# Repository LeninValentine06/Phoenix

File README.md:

# LoRa-Based Real-Time Landslide Detection System
   
   *Figure 1: Slave Node PCB Design*

   *Figure 2: Master Node PCB Design*

## 1. Project Overview

### The Problem

Landslides are devastating natural disasters that claim thousands of lives annually worldwide. Traditional monitoring systems are often expensive, difficult to deploy in remote areas, and lack real-time alerting capabilities. Many vulnerable communities, especially in developing regions, lack access to early warning systems that could save lives.

### Our Solution

The LoRa-Based Real-Time Landslide Detection System provides an affordable, open-source solution for early detection and warning of potential landslide events. By combining low-power sensors, long-range wireless communication, and intelligent data processing, our system can:

- Detect early signs of land movement and soil condition changes
- Transmit data over long distances even in remote areas
- Provide immediate, multi-modal alerts to communities at risk
- Operate for extended periods on battery power

The system uses distributed ESP32-based sensor nodes placed in landslide-prone areas to continuously monitor ground movement, soil moisture, and environmental conditions. When potential landslide indicators are detected, the system triggers immediate alerts via multiple channels.

## 2. System Architecture

### Hardware Components

#### Sensor Node (ESP32)
- **Microcontroller**: ESP32-WROOM-32
- **Sensors**:
  - MPU6050 (3-axis accelerometer and gyroscope)
  - Capacitive soil moisture sensor
  - DHT22/AM2302 temperature and humidity sensor
- **Communication**: LoRa RA-02 module (433MHz)
- **Power**: 3.7V LiPo battery with solar charging capability

#### Master Node (ESP32)
- **Microcontroller**: ESP32-WROOM-32
- **Alert Mechanisms**:
  - 9V speaker/buzzer for audio alerts
  - 2.8" ILI9341 TFT display for visual alerts and status
  - Optional GSM module for SMS alerts
- **Communication**:
  - LoRa RA-02 module (433MHz)
  - WiFi/Bluetooth (for configuration and notifications)
- **Power**: 5V DC power supply with battery backup

### Data Flow Architecture

```
┌─────────────────┐     LoRa     ┌─────────────────┐     Alert     ┌─────────────────┐
│                 │  Wireless    │                 │   Triggers    │                 │
│   Sensor Node   │ ───────────► │   Master Node   │ ───────────► │  Alert Systems  │
│     (ESP32)     │    433MHz    │     (ESP32)     │               │   - Speaker     │
│                 │              │                 │               │   - Display     │
│                 │              │                 │               │   - Mobile      │
└─────────────────┘              └─────────────────┘               └─────────────────┘
        │                                 ▲
        │                                 │
        │         LoRa Wireless           │
        └─────────────────────────────────┘
                (Multiple Nodes)
```

1. **Data Collection**: The ESP32 sensor nodes continuously monitor accelerometer data (ground movement), soil moisture levels, and environmental conditions.
2. **Data Processing**: Initial data processing occurs on the sensor nodes to identify concerning patterns before transmission.
3. **Data Transmission**: Processed data is transmitted via LoRa to the master node.
4. **Alert Analysis**: The ESP32 master node analyzes data from multiple sensor nodes and determines if alert thresholds are exceeded.
5. **Alert Distribution**: When potential landslide conditions are detected, the master node activates local alerts and sends notifications to configured devices.

## 3. Features

### Real-time Environmental Monitoring
- Continuous accelerometer data collection at 50Hz sample rate
- Soil moisture monitoring with 5-minute intervals
- Temperature and humidity readings every 15 minutes
- Local data processing to detect movement patterns indicative of landslides

### Long-Range, Low-Power Communication
- LoRa communication with 3-10km range (depending on terrain) using 433MHz frequency
- Optimized data packets to minimize transmission power
- Node power management for extended battery life (3-6 months on a single charge with solar support)
- Reliable mesh networking capabilities between multiple sensor nodes

### Multi-Modal Alert System
- High-decibel audio alarm for immediate local warning
- Visual alerts and system status on TFT display
- Optional mobile alerts via SMS or app notifications
- Configurable alert thresholds based on local conditions

### System Scalability
- Support for up to 50 sensor nodes per master node
- Expandable with multiple master nodes for larger coverage areas
- Modular design allowing for additional sensor types
- Open API for integration with existing warning systems

## 4. Setup & Installation

### Prerequisites

#### Hardware Requirements
- ESP32 development boards (for both sensor and master nodes)
- MPU6050 accelerometer/gyroscope module
- Soil moisture sensor (capacitive recommended)
- DHT22/AM2302 temperature & humidity sensor
- LoRa RA-02 modules (433MHz)
- 2.8" ILI9341 TFT display
- 9V speaker/buzzer
- 3.7V LiPo batteries with solar charging modules
- Power supplies, jumper wires, and prototyping boards

#### Software Requirements
- Arduino IDE (for ESP32 programming)
- Required libraries (included in the repository):
  - RadioHead library for LoRa communication
  - Adafruit MPU6050 library
  - Adafruit DHT sensor library
  - Adafruit GFX & ILI9341 libraries

### Sensor Node Setup

1. **Hardware Assembly**

   Connect the components to the ESP32 according to this pinout:
   
   ```
   ESP32 (Sensor Node)   |     Component
   ------------------------------------
   GPIO21 (SDA)         ---    MPU6050 SDA
   GPIO22 (SCL)         ---    MPU6050 SCL
   GPIO36 (ADC0)        ---    Soil Moisture Sensor
   GPIO17               ---    DHT22 Data
   GPIO5 (SCK)          ---    RA-02 SCK
   GPIO23 (MOSI)        ---    RA-02 MOSI
   GPIO19 (MISO)        ---    RA-02 MISO
   GPIO18               ---    RA-02 CS
   GPIO14               ---    RA-02 RST
   GPIO26               ---    RA-02 DIO0
   5V                   ---    Battery + (via switch)
   GND                  ---    Common ground
   ```

*Figure 3: Serial Monitor Output from Slave Node showing sensor readings and LoRa transmission*

2. **Software Installation**

   a. Setup Arduino IDE for ESP32:
   - Add ESP32 board support to Arduino IDE
   - Install required libraries through the Library Manager

   b. Upload the sensor node code:
   - Clone this repository: `git clone https://github.com/LeninValentine06/lora-landslide-detection.git`
   - Navigate to the `sensor_node` directory
   - Open the `sensor_node.ino` file
   - Select your ESP32 board model and port
   - Compile and upload the code

### Master Node Setup

1. **Hardware Assembly**

   Connect the components to the ESP32 according to this pinout:
   
   ```
   ESP32 (Master Node)   |     Component
   ------------------------------------
   GPIO5 (SCK)          ---    RA-02 SCK
   GPIO23 (MOSI)        ---    RA-02 MOSI
   GPIO19 (MISO)        ---    RA-02 MISO
   GPIO18               ---    RA-02 CS
   GPIO14               ---    RA-02 RST
   GPIO26               ---    RA-02 DIO0
   GPIO25               ---    Speaker +
   GPIO21 (SDA)         ---    Display SDA
   GPIO22 (SCL)         ---    Display SCL
   GPIO2                ---    Display DC
   GPIO4                ---    Display CS
   GPIO15               ---    Display RST
   5V                   ---    Power input
   GND                  ---    Common ground
   ```

*Figure 4: Serial Monitor Output from Master Node showing received data and alert status*

2. **Software Installation**

   a. Setup Arduino IDE for ESP32:
   - Add ESP32 board support to Arduino IDE
   - Install required libraries through the Library Manager

   b. Upload the master node code:
   - Open the `/master_node/master_node.ino` file from the repository
   - Select your ESP32 board model and port
   - Compile and upload the code

### Optional Mobile Notification Setup

1. Install the companion mobile app (available in the `/mobile_app` directory)
2. Configure WiFi credentials in the master node code
3. Pair your smartphone with the master node using the app
4. Test the notification system by triggering a test alert

## 5. Usage Instructions

### Initial Configuration

1. Place sensor nodes in strategic locations based on landslide risk assessment
   - Ensure proper anchoring into stable ground
   - Position solar panels for optimal sunlight exposure
   - Maintain line-of-sight between nodes when possible

2. Power on the master node first, then the sensor nodes
   - The master node display will show initialization progress
   - Wait for "SYSTEM READY" message on the display

3. Configure alert thresholds using the master node interface:
   - Press the CONFIG button to enter setup mode
   - Adjust sensitivity, alert levels, and communication parameters
   - Save configuration when complete

### Normal Operation

Under normal conditions, the system will:
- Display current readings from all sensor nodes
- Show battery levels and signal strength
- Log data at regular intervals
- Perform automatic self-tests every 24 hours

The TFT display shows a grid of connected sensor nodes with their status. Green indicators show normal operation, yellow shows warning levels, and red indicates critical alerts.

### Alert Conditions

When potential landslide conditions are detected:

1. The master node will:
   - Activate the audio alarm
   - Display detailed alert information
   - Send notifications to paired mobile devices
   - Log the event with timestamp and sensor data

2. To acknowledge alerts:
   - Press the ACKNOWLEDGE button on the master node
   - The audio alarm will silence, but visual alerts remain
   - The system continues monitoring for worsening conditions

3. After the danger passes:
   - Press and hold RESET for 5 seconds
   - Confirm system reset when prompted
   - The system will return to normal monitoring mode

## 6. Contributing

Contributions to this project are welcome! Here's how you can help:

### Reporting Issues
- Use the GitHub issue tracker to report bugs
- Include detailed steps to reproduce the issue
- Attach logs or screenshots when available

### Pull Requests
1. Fork the repository
2. Create a new branch (`git checkout -b feature/your-feature-name`)
3. Make your changes
4. Run tests if available
5. Commit your changes (`git commit -m 'Add some feature'`)
6. Push to the branch (`git push origin feature/your-feature-name`)
7. Open a Pull Request

### Development Guidelines
- Follow existing code style and naming conventions
- Add comments to explain complex functionality
- Update documentation when making changes
- Add tests for new features when possible

## 7. License

This project is licensed under the Creative Commons Zero v1.0 Universal License - see the [LICENSE](LICENSE) file for details.

This means you can copy, modify, distribute and perform the work, even for commercial purposes, all without asking permission.

---

**Disclaimer**: This system is designed as an early warning tool but should not replace proper evacuation procedures or professional geological assessment. Always follow local authority guidance during emergency situations.

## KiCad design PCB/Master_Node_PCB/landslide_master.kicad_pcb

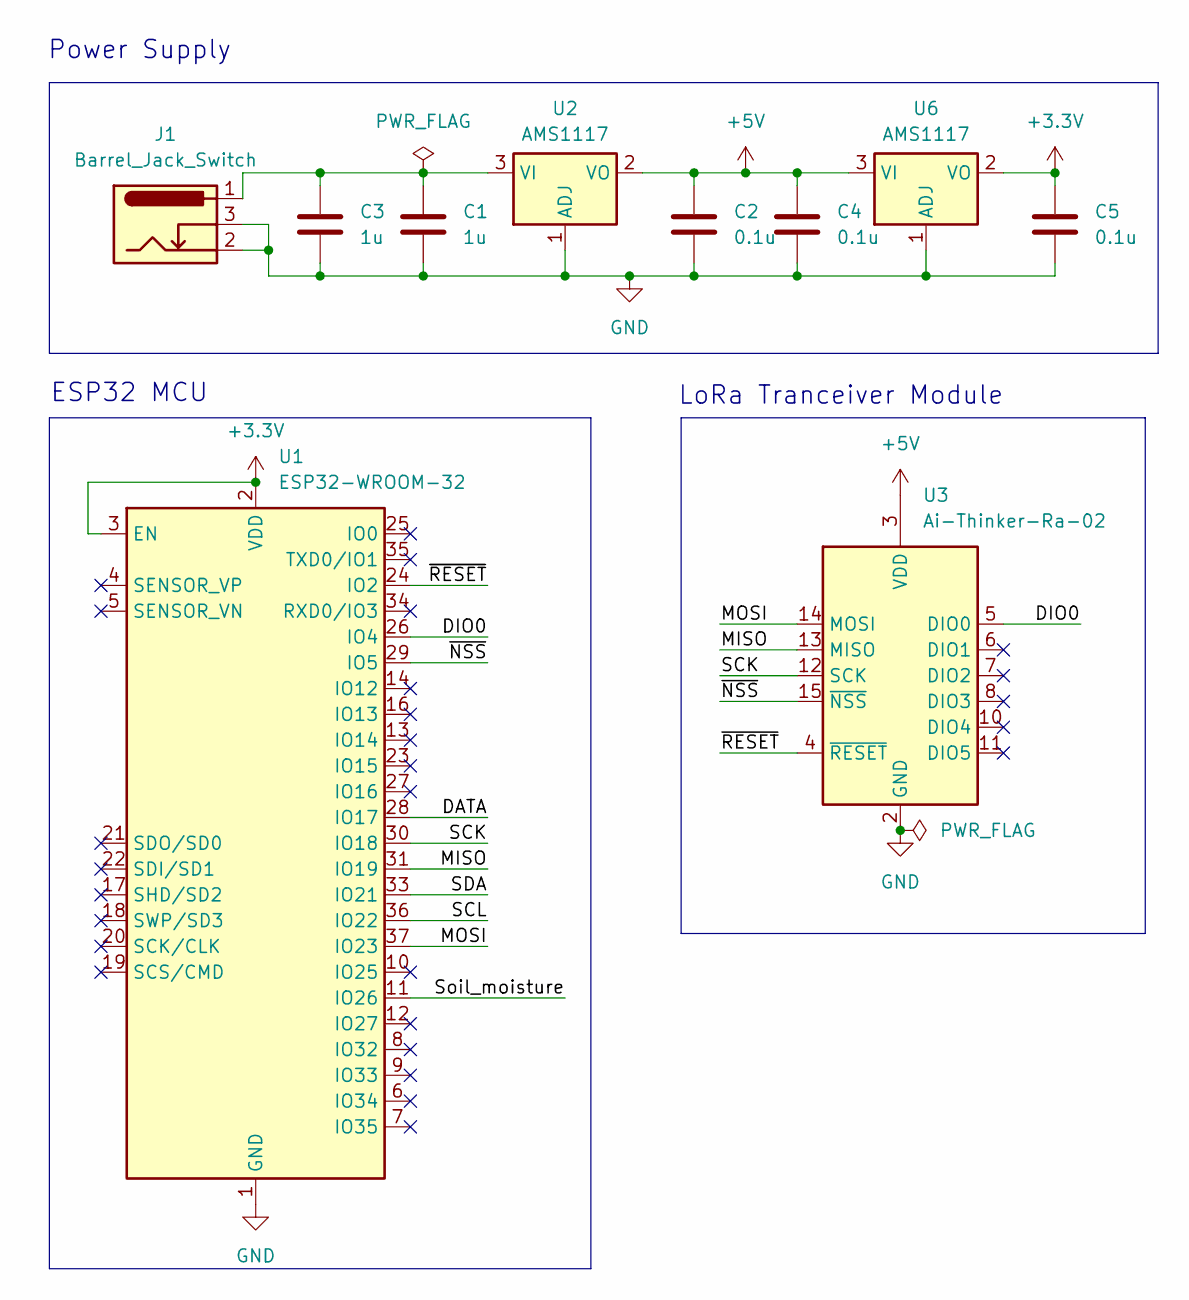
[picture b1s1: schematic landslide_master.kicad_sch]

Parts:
C1, C3: 1u; C_0805_2012Metric
C2, C4, C5: 0.1u; C_0805_2012Metric
J1: Barrel_Jack_Switch; BarrelJack_Horizontal
U1: ESP32-WROOM-32
U2, U6: AMS1117; SOT-223-3_TabPin2
U3: Ai-Thinker-Ra-02; Ai-Thinker-Ra-01-LoRa

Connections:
+3.3V: C5.1, U1.2 (VDD), U1.3 (EN), U6.2 (VO)
+5V: C2.1, C4.1, U2.2 (VO), U3.3 (VDD), U6.3 (VI)
/DATA: U1.28 (IO17)
/DIO0: U1.26 (IO4), U3.5 (DIO0)
/MISO: U1.31 (IO19), U3.13 (MISO)
/MOSI: U1.37 (IO23), U3.14 (MOSI)
/SCK: U1.30 (IO18), U3.12 (SCK)
/SCL: U1.36 (IO22)
/SDA: U1.33 (IO21)
/Soil_moisture: U1.11 (IO26)
/~NSS: U1.29 (IO5), U3.15 (~NSS)
/~RESET: U1.24 (IO2), U3.4 (~RESET)
GND: C1.2, C2.2, C3.2, C4.2, C5.2, J1.2, J1.3, U1.1 (GND), U1.15 (GND), U1.38 (GND), U1.39 (GND), U2.1 (ADJ), U3.1 (GND), U3.2 (GND), U3.9 (GND), U3.16 (GND), U6.1 (ADJ)
unnamed: C1.1, C3.1, J1.1, U2.3 (VI)

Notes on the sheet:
ESP32 MCU
Power Supply
LoRa Tranceiver Module

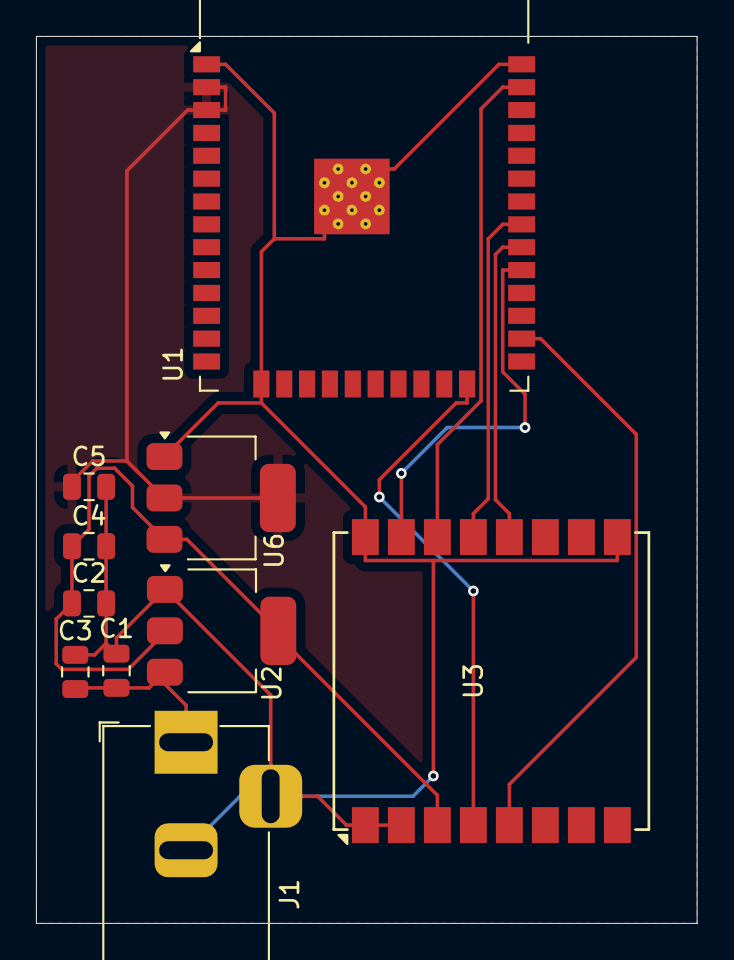
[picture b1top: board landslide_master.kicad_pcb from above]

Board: 2 copper layers, 36.7 x 49.3 mm, 10 parts (0 on the bottom side), 10 nets.

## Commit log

2025-03-15 Added master_node and slave_node files
2025-03-15 Added mobile_app files
2025-03-15 Added PCB files
2025-03-15 Updated files
